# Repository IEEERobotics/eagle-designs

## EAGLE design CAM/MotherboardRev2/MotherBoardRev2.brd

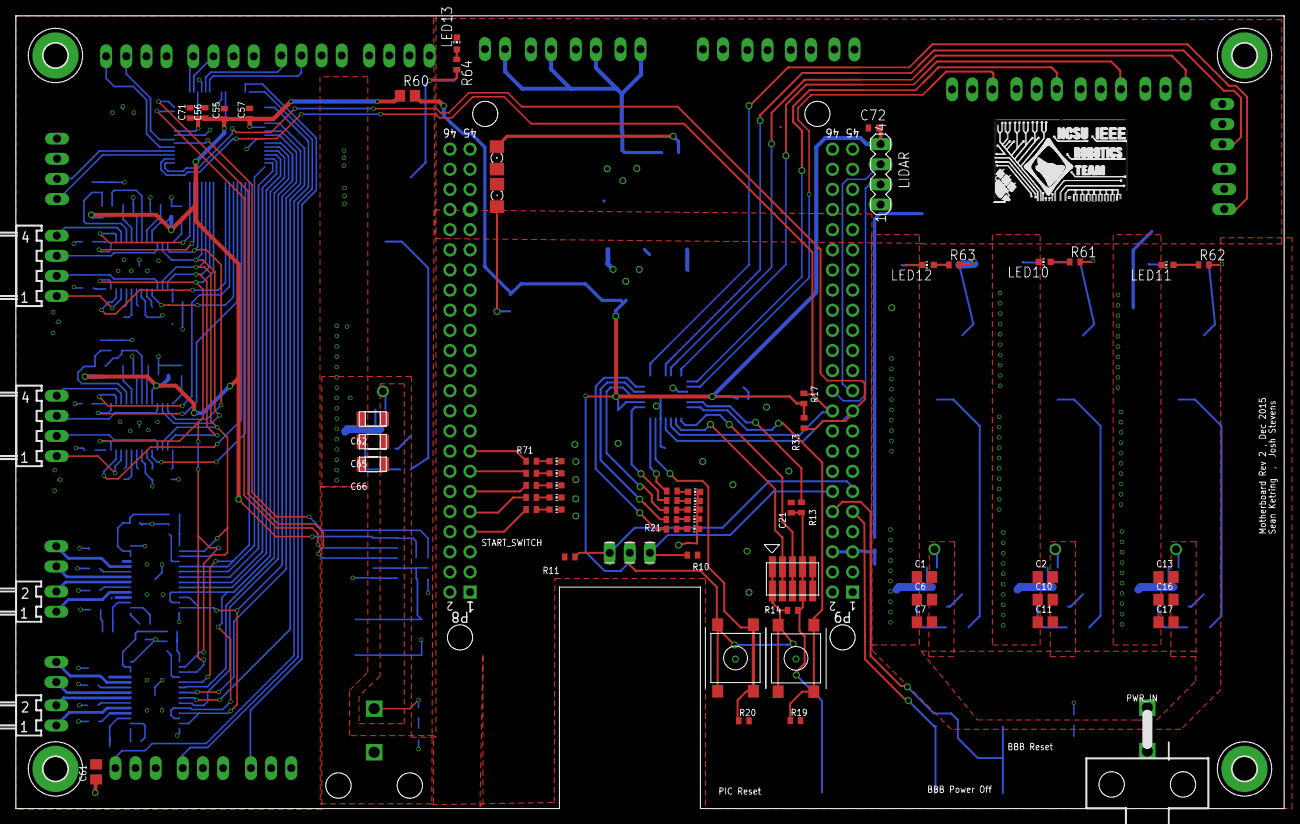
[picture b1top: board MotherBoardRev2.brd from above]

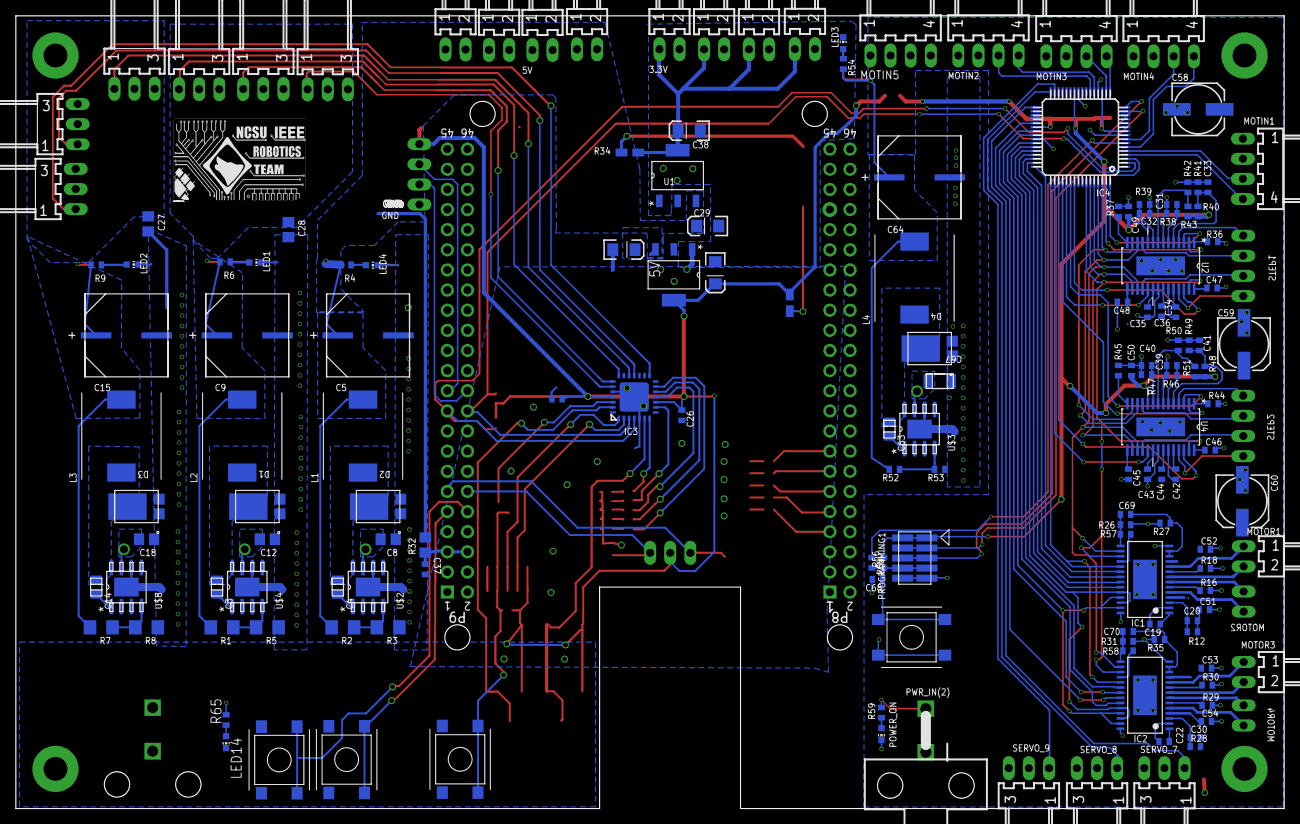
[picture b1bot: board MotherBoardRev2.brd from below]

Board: 2 copper layers, 160.0 x 100.0 mm, 232 parts (157 on the bottom side), 164 nets.

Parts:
3.3V, 3.3V1, 3.3V(2), 3.3V(2)1, 5V, 5V1, 5V(2), 5V(2)1: 7395-02
C1, C2, C6, C7, C8, C10, C11, C12, C13, C16, C17, C18: 4.7uF; C0805
C3, C4, C14, C63: 10nF; 0805
C5, C9, C15, C64: 330uF; SM_RADIAL_10AMM
C19, C22, C51, C52, C53, C54: 0.01uF; C0402
C20, C30, C33, C45, C46, C47, C48, C49, C50, C56, C57, C71: 0.1uF; C0402
C21, C25, C26, C37, C41, C68: .1uF; C0402
C23, C24, C29, C38: 10uF; EIA3216
C27, C28, C61: 10uF; C0805
C31, C32, C39, C40: 1nF; C0402
C34, C35, C36, C42, C43, C44: 0.22uF; C0402
C55: 1uF; C0402
C58, C59, C60: 153CLV-0605
C62, C65, C66, C67: 4.7uF; 1206
C69, C70: 0.47uF; C0402
C72: 4.7uF; C0402
D1, D2, D3, D4: PDS760-13; POWERDI5
D5, D7: 3_3V_PWR; FKIT-LED-1206
H1, H2, H3, H4: MOUNT-PAD-ROUND3.0; 3,0-PAD
IC1, IC2: DRV8814; TSSOP-28
IC3: PIC24FJ64GB202; QFN28-ML_6X6MM
IC4: PIC24FJ256GB106; TQFP64-10X10
L1, L2, L3, L4: WE-HCC_1090
LED1, LED2, LED3, LED4, LED5, LED6, LED7, LED8, LED9, LED10, LED11, LED12, LED13, LED14, LED16, LED17, LED18, LED19, LED20: CHIP-LED0603
LIDAR: MA04-1
MOTIN1, MOTIN2, MOTIN3, MOTIN4, MOTIN5: 22-05-7048-04; 7395-04
MOTOR1, MOTOR2, MOTOR3, MOTOR4: 22-05-7028-02; 7395-02
POWER_ON: CHIP-LED0603
PROGRAMMING, PROGRAMMING1: Jtag; MOTHER-BOARD-REV5_10-PIN-SMD
PWR_IN: 5569-2
PWR_IN(2): 5569-2
R1, R2, R7: 10k; R1206
R3, R5, R8: R1206
R4, R6, R9, R14, R26, R31, R40, R41, R42, R43, R48, R49, R50, R51, R52, R54, R56, R57, R58, R59, R61, R62, R63, R64, R65: 10k; R0402
R10, R11, R19, R20: 10K; R0402
R12, R28: 1M; R0402
R13, R55: 100; R0402
R15, R34: R0805W
R16, R18, R29, R30: 0.2; R0402
R17, R33: 4.7K; R0402
R21, R22, R23, R24, R25: 330; R0402
R27, R35: 30k; R0402
R32: 0 ohm; R0805
R36, R37, R44, R45: 0.1; R0402
R38, R39, R46, R47: 47k; R0402
R53: R0402
R60: R0805
R67, R68, R69, R70, R71: 1K; R0402
SERVO_1, SERVO_2, SERVO_3, SERVO_4, SERVO_5, SERVO_6, SERVO_7, SERVO_8, SERVO_9: 7395-03
START_SWITCH: MA03-1
STEP1, STEP2: 22-05-7048-04; 7395-04
U1, U3: LMS8117AMP-3.3; SOT230P696X180-4N
U2, U4: DRV8811PWP; SOP65P640X120-29N
U$1: BEAGLE_BONE_BLACK_CAPE
U$2, U$3, U$4, U$8: TPS5450DDAR; R-PDSO-G8
U$5, U$9: Switch3; MC32882_FINAL
U$6, U$13, U$14: Switch1; MC32882_FINAL
U$7: Switch2; MC32882_FINAL
U$10, U$11, U$12: LOGO

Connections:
3.3V: C24.A, C25.1, C26.1, C49.1, C50.1, C55.1, C56.1, C57.1, C71.1, C72.1, IC3.10, IC3.25, IC4.10, IC4.19, IC4.26, IC4.38, LIDAR.4, PROGRAMMING.1, PROGRAMMING.2, PROGRAMMING1.1, PROGRAMMING1.2, R14.2, R15.1, R17.2, R33.2, R40.1, R43.1, R48.1, R51.1, R56.2, R60.1, R60.2, START_SWITCH.2, U2.10, U3.4, U4.10, U$6.P$1, U$6.P$4, U$7.P$1, U$7.P$4
+7V: C20.2, C30.2, C36.1, C44.1, C45.1, C46.1, C47.1, C48.1, C51.1, C52.1, C53.1, C54.1, C58.+, C59.+, C60.+, C61.1, C64.1, H4.B3,0, IC1.4, IC1.11, IC2.4, IC2.11, L4.2, MOTIN1.2, MOTIN2.2, MOTIN3.2, MOTIN4.2, MOTIN5.2, MOTIN5.3, R12.2, R28.2, R52.2, R54.2, R64.2, SERVO_7.2, SERVO_8.2, SERVO_9.2, U2.15, U2.28, U4.15, U4.28
BB_PWR_BUTTON: U$1.P9.9, U$13.P$2, U$13.P$3
BB_SYS_RESET: U$1.P9.10, U$14.P$2, U$14.P$3
BOOT1: C4.1, U$2.1
BOOT2: C3.1, U$4.1
BOOT3: C14.1, U$8.1
BOOT_VM: C63.1, U$3.1
CHANNEL_A_1: IC4.4, MOTIN1.4
CHANNEL_A_2: IC4.22, MOTIN2.3
CHANNEL_A_3: IC4.18, MOTIN3.3
CHANNEL_A_4: IC4.8, MOTIN4.3
CHANNEL_B_1: IC4.5, MOTIN1.3
CHANNEL_B_2: IC4.21, MOTIN2.4
CHANNEL_B_3: IC4.17, MOTIN3.4
CHANNEL_B_4: IC4.6, MOTIN4.4
GND: 3.3V.2, 3.3V1.2, 3.3V(2).2, 3.3V(2)1.2, 5V.2, 5V1.2, 5V(2).2, 5V(2)1.2, C1.1, C2.1, C5.2, C6.1, C7.1, C8.1, C9.2, C10.1, C11.1, C12.1, C13.1, C15.2, C16.1, C17.1, C18.1, C21.2, C23.C, C24.C, C25.2, C26.2, C27.2, C28.2, C29.C, C31.2, C32.2, C33.2, C35.2, C37.2, C38.C, C39.2, C40.2, C41.2, C43.2, C45.2, C46.2, C47.2, C48.2, C49.2, C50.2, C51.2, C52.2, C53.2, C54.2, C55.2, C56.2, C57.2, C58.-, C59.-, C60.-, C61.2, C62.1, C64.2, C65.1, C66.1, C67.1, C68.2, C69.2, C70.2, C71.2, C72.2, D1.1, D2.1, D3.1, D4.1, D5.C, D7.C, IC1.14, IC1.28, IC1.EXP, IC2.14, IC2.28, IC2.EXP, IC3.5, IC3.24, IC3.EXP, IC4.9, IC4.20, IC4.25, IC4.41, LED1.C, LED2.C, LED3.C, LED4.C, LED5.C, LED6.C, LED7.C, LED8.C, LED9.C, LED10.C, LED11.C, LED12.C, LED13.C, LED14.C, LED16.C, LED17.C, LED18.C, LED19.C, LED20.C, LIDAR.1, MOTIN1.1, MOTIN2.1, MOTIN3.1, MOTIN4.1, MOTIN5.1, MOTIN5.4, POWER_ON.C, PROGRAMMING.9, PROGRAMMING.10, PROGRAMMING1.9, PROGRAMMING1.10, PWR_IN.1, PWR_IN(2).1, R3.1, R5.1, R8.1, R10.1, R11.1, R16.2, R18.2, R19.2, R20.2, R27.2, R29.2, R30.2, R35.2, R36.2, R37.2, R38.2, R39.2, R41.2, R42.2, R44.2, R45.2, R46.2, R47.2, R49.2, R50.2, R53.1, SERVO_1.3, SERVO_2.3, SERVO_3.3, SERVO_4.3, SERVO_5.3, SERVO_6.3, SERVO_7.3, SERVO_8.3, SERVO_9.3, U1.1, U2.7, U2.21, U2.29, U3.1, U4.7, U4.21, U4.29, U$1.P8.1, U$1.P8.2, U$1.P9.1, U$1.P9.2, U$1.P9.43, U$1.P9.44, U$1.P9.45, U$1.P9.46, U$2.6, U$2.9, U$3.6, U$3.9, U$4.6, U$4.9, U$5.P$1, U$5.P$4, U$8.6, U$8.9, U$9.P$1, U$9.P$4, U$13.P$1, U$13.P$4, U$14.P$1, U$14.P$4
GPIO23: R70.2, U$1.P8.13
GPIO45: R69.2, U$1.P8.11
GPIO47: R71.2, U$1.P8.15
GPIO66: R67.2, U$1.P8.7
GPIO69: R68.2, U$1.P8.9
IO3: IC3.7, R25.2
IO4: IC3.9, R24.2
IO5: IC3.11, R23.2
IO6: IC3.12, R22.2
IO7: IC3.13, R21.2
M1-AENBL: IC1.21, IC4.47
M1-APHASE: IC1.20, IC4.48
M1-BENBL: IC1.22, IC4.46
M1-BHPASE: IC1.23, IC4.45
M1-MAOUT1: IC1.5, MOTOR2.1
M1-MAOUT2: IC1.7, MOTOR2.2
M1-MBOUT1: IC1.10, MOTOR1.1
M1-MBOUT2: IC1.8, MOTOR1.2
M2-AENBL: IC2.21, IC4.39
M2-APHASE: IC2.20, IC4.43
M2-BENBL: IC2.22, IC4.37
M2-BHPASE: IC2.23, IC4.42
M2-MAOUT1: IC2.5, MOTOR4.1
M2-MAOUT2: IC2.7, MOTOR4.2
M2-MBOUT1: IC2.10, MOTOR3.1
M2-MBOUT2: IC2.8, MOTOR3.2
M-DECAY: IC1.19, IC2.19, IC4.49
M-I0: IC1.24, IC1.26, IC2.24, IC2.26, IC4.44
M-I1: IC1.25, IC1.27, IC2.25, IC2.27, IC4.40
M-NSLEEP: IC1.17, IC2.17, IC4.58, U2.27, U4.27
M-RESET: IC1.16, IC2.16, IC4.60, U2.17, U4.17
MCLR: C21.1, PROGRAMMING.7, PROGRAMMING.8, R13.2, R14.1, U$5.P$2, U$5.P$3
MCLR': IC3.26, R13.1
M_MCLR: C68.1, PROGRAMMING1.7, PROGRAMMING1.8, R55.2, R56.1, U$9.P$2, U$9.P$3
M_MCLR': IC4.7, R55.1
M_PGC1: IC4.15, PROGRAMMING1.3, PROGRAMMING1.4
M_PGD1: IC4.16, PROGRAMMING1.5, PROGRAMMING1.6
unnamed: LED4.A, R4.1
unnamed: LED1.A, R6.1
unnamed: LED2.A, R9.1
unnamed: C19.2, IC1.2
unnamed: LED5.A, R21.1
unnamed: LED6.A, R22.1
unnamed: LED7.A, R23.1
unnamed: LED8.A, R24.1
unnamed: LED9.A, R25.1
unnamed: D5.A, R15.2
unnamed: D7.A, R34.2
unnamed: C19.1, IC1.1
unnamed: C20.1, IC1.3, R12.1
unnamed: IC1.6, R16.1
unnamed: IC1.9, R18.1
unnamed: IC1.12, IC1.13, R26.1, R27.1
unnamed: C22.2, IC2.2
unnamed: C37.1, R32.1, U$1.P9.5, U$1.P9.6
unnamed: LED14.A, R65.1
unnamed: C22.1, IC2.1
unnamed: C30.1, IC2.3, R28.1
unnamed: IC2.6, R29.1
unnamed: IC2.9, R30.1
unnamed: IC2.12, IC2.13, R31.1, R35.1
unnamed: IC1.18, R57.1
unnamed: R37.1, U2.14
unnamed: R36.1, U2.1
unnamed: C69.1, IC1.15, R26.2, R57.2
unnamed: C31.1, R38.1, U2.6
unnamed: C32.1, R39.1, U2.9
unnamed: C33.1, R40.2, R41.1, U2.5
unnamed: R42.1, R43.2, U2.8
unnamed: IC2.18, R58.1
unnamed: C34.1, U2.23
unnamed: C70.1, IC2.15, R31.2, R58.2
unnamed: C34.2, U2.24
unnamed: C35.1, U2.20
unnamed: C36.2, U2.22
unnamed: R45.1, U4.14
unnamed: R44.1, U4.1
unnamed: C39.1, R46.1, U4.6
unnamed: C40.1, R47.1, U4.9
unnamed: C41.1, R48.2, R49.1, U4.5
unnamed: R50.1, R51.2, U4.8
unnamed: C42.1, U4.23
unnamed: C42.2, U4.24
unnamed: C43.1, U4.20
unnamed: C44.2, U4.22
unnamed: LED3.A, R54.1
unnamed: POWER_ON.A, R59.1
unnamed: LED16.A, R67.1
unnamed: LED17.A, R68.1
unnamed: LED18.A, R69.1
unnamed: LED19.A, R70.1
unnamed: LED20.A, R71.1
unnamed: LED10.A, R61.1
unnamed: LED11.A, R62.1
unnamed: LED12.A, R63.1
unnamed: LED13.A, R64.1
OC1: IC3.23, SERVO_6.1
OC1': IC4.33, SERVO_7.1
OC2: IC3.22, SERVO_5.1
OC2': IC4.32, SERVO_8.1
OC3: IC3.21, SERVO_4.1
OC3': IC4.31, SERVO_9.1
OC4: IC3.19, SERVO_3.1
OC5: IC3.18, SERVO_2.1
OC6: IC3.15, SERVO_1.1
PGC1: IC3.2, PROGRAMMING.3, PROGRAMMING.4
PGD1: IC3.1, PROGRAMMING.5, PROGRAMMING.6
PH1: C4.2, D2.3, L1.1, U$2.8
PH2: C3.2, D1.3, L2.1, U$4.8
PH3: C14.2, D3.3, L3.1, U$8.8
PH_VM: C63.2, D4.3, L4.1, U$3.8
S1-AOUT1: STEP1.4, U2.4
S1-AOUT2: STEP1.1, U2.25
S1-BOUT1: STEP1.3, U2.11
S1-BOUT2: STEP1.2, U2.18
S1-DIR: IC4.64, U2.3
S1-ENABLEN: IC4.55, U2.26
S1-HOME: IC4.63, U2.2
S1-STEP: IC4.53, U2.19
S2-AOUT1: STEP2.4, U4.4
S2-AOUT2: STEP2.1, U4.25
S2-BOUT1: STEP2.3, U4.11
S2-BOUT2: STEP2.2, U4.18
S2-DIR: IC4.54, U4.3
S2-ENABLEN: IC4.51, U4.26
S2-HOME: IC4.52, U4.2
S2-STEP: IC4.50, U4.19
S-SRN: IC4.59, U2.16, U4.16
SCL: IC3.4, IC4.2, R33.1, U$1.P9.19
SDA: IC3.3, IC4.3, R17.1, U$1.P9.20
START_LEFT: R10.2, START_SWITCH.3, U$1.P9.12
START_RIGHT: R11.2, START_SWITCH.1, U$1.P9.11
SWITCH_1: IC3.27, R19.1, U$6.P$2, U$6.P$3
SWITCH_2: IC3.6, R20.1, U$7.P$2, U$7.P$3
UART_RX: LIDAR.2, U$1.P9.22
UART_TX: LIDAR.3, U$1.P9.21
USM0: IC4.62, U2.13, U4.13
USM1: IC4.61, U2.12, U4.12
VCC: C1.2, C2.2, C6.2, C7.2, C8.2, C10.2, C11.2, C12.2, C13.2, C16.2, C17.2, C18.2, C62.2, C65.2, C66.2, C67.2, PWR_IN.2, PWR_IN(2).2, R59.2, R65.2, U$2.7, U$3.7, U$4.7, U$8.7
VOUT1: 5V.1, 5V1.1, 5V(2).1, 5V(2)1.1, C5.1, C23.A, C29.A, L1.2, R2.2, R4.2, R32.2, R63.2, U1.3, U3.3
VOUT2: C9.1, C28.1, L2.2, R1.2, R6.2, R61.2, SERVO_4.2, SERVO_5.2, SERVO_6.2
VOUT3: C15.1, C27.1, L3.2, R7.2, R9.2, R62.2, SERVO_1.2, SERVO_2.2, SERVO_3.2
VOUT5: 3.3V.1, 3.3V1.1, 3.3V(2).1, 3.3V(2)1.1, C38.A, R34.1, U1.4
VSNS1: R2.1, R3.2, U$2.4
VSNS2: R1.1, R5.2, U$4.4
VSNS3: R7.1, R8.2, U$8.4
VSNS_VM: R52.1, R53.2, U$3.4

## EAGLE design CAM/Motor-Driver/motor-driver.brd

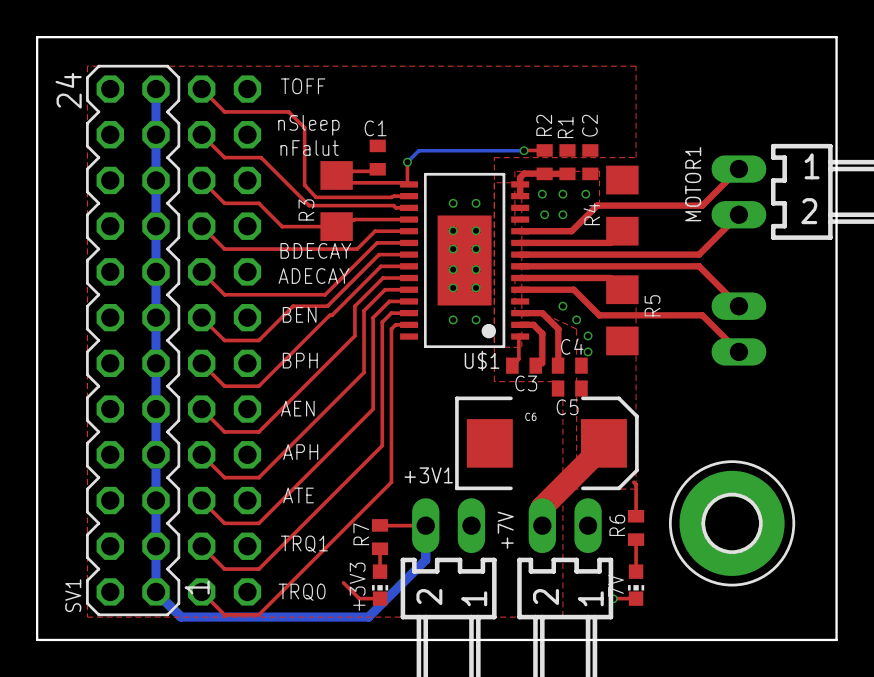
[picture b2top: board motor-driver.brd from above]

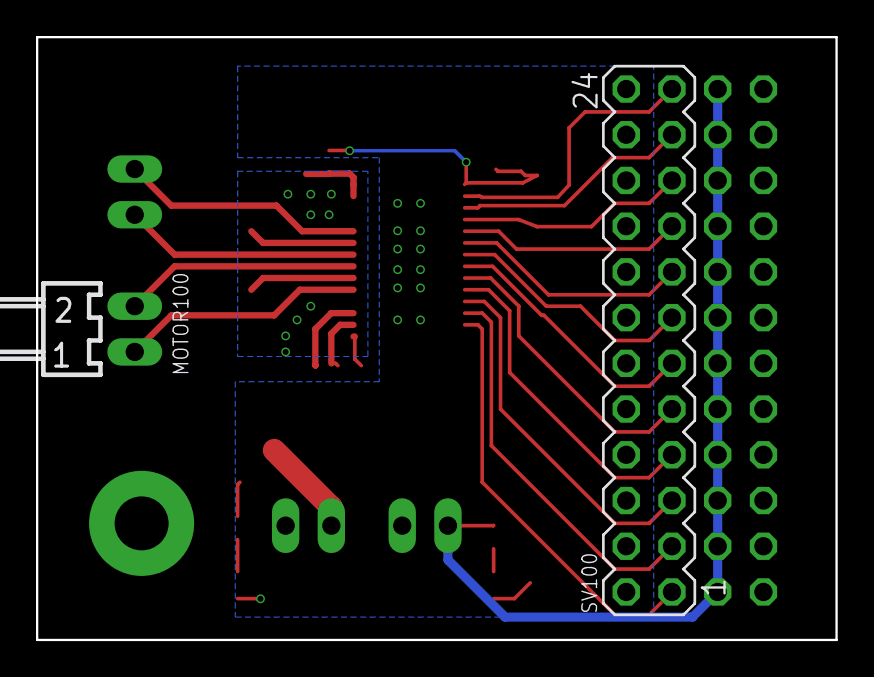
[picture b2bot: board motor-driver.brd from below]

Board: 2 copper layers, 44.4 x 33.5 mm, 23 parts (2 on the bottom side), 28 nets.

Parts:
7V: CHIP-LED0603
+3V1, +7V: 22-05-7028-02; 7395-02
+3V3: CHIP-LED0603
C1, C2, C3, C5: 0.1uF; C0402
C4: 0.47uF; C0402
C6: 100uF; EIA7343
H1: MOUNT-PAD-ROUND3.0; 3,0-PAD
MOTOR1, MOTOR100: 22-05-7028-02; 7395-02
R1, R2: 0.2; R0402
R3: 10K; R1206
R4, R5: R1206
R6: 700; R0402
R7: 330; R0402
SV1, SV100: MA12-2
U$1: DRV8881PPWPR; TSSOP-28

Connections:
+3V3: +3V1.2, R7.2, SV1.1, SV1.3, SV1.5, SV1.7, SV1.9, SV1.11, SV1.13, SV1.15, SV1.17, SV1.19, SV1.21, SV1.23
+7V: +7V.2, C2.1, C4.2, C5.1, C6.A, R6.2, U$1.4, U$1.11
ADECAY: SV100.15, U$1.20
AEN: SV100.9, U$1.23
APH: SV100.7, U$1.24
ATE: SV100.5, U$1.25
BDECAY: SV100.17, U$1.19
BEN: SV100.13, U$1.21
BPH: SV100.11, U$1.22
GND: 7V.C, +3V1.1, +3V3.C, +7V.1, C1.2, C2.2, C5.2, C6.C, R2.2, SV100.2, SV100.4, SV100.6, SV100.8, SV100.10, SV100.12, SV100.14, SV100.16, SV100.18, SV100.20, SV100.22, SV100.24, U$1.12, U$1.28, U$1.EXP
unnamed: R4.1, U$1.9
unnamed: R5.1, U$1.6
unnamed: MOTOR100.1, U$1.5
unnamed: MOTOR100.2, U$1.7
unnamed: MOTOR1.2, U$1.8
unnamed: MOTOR1.1, U$1.10
unnamed: C3.2, U$1.2
unnamed: C3.1, U$1.1
unnamed: C4.1, U$1.3
unnamed: +3V3.A, R7.1
unnamed: 7V.A, R6.1
unnamed: R1.2, R2.1, U$1.13, U$1.14
NFAULT: R3.1, SV100.19, U$1.18
NSLEEP: SV100.21, U$1.17
TOFF: SV100.23, U$1.16
TRQ0: SV100.1, U$1.27
TRQ1: SV100.3, U$1.26
V3P3: C1.1, R1.1, R3.2, U$1.15

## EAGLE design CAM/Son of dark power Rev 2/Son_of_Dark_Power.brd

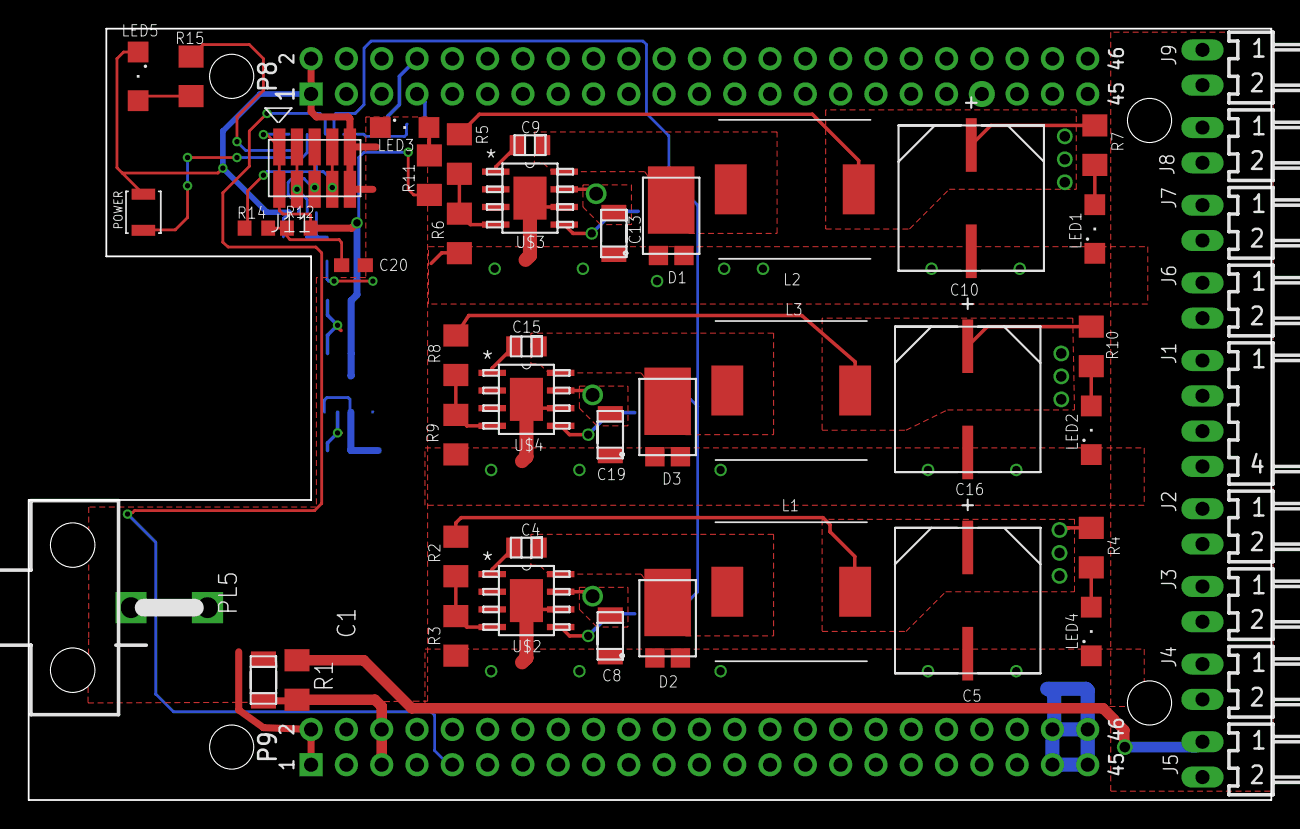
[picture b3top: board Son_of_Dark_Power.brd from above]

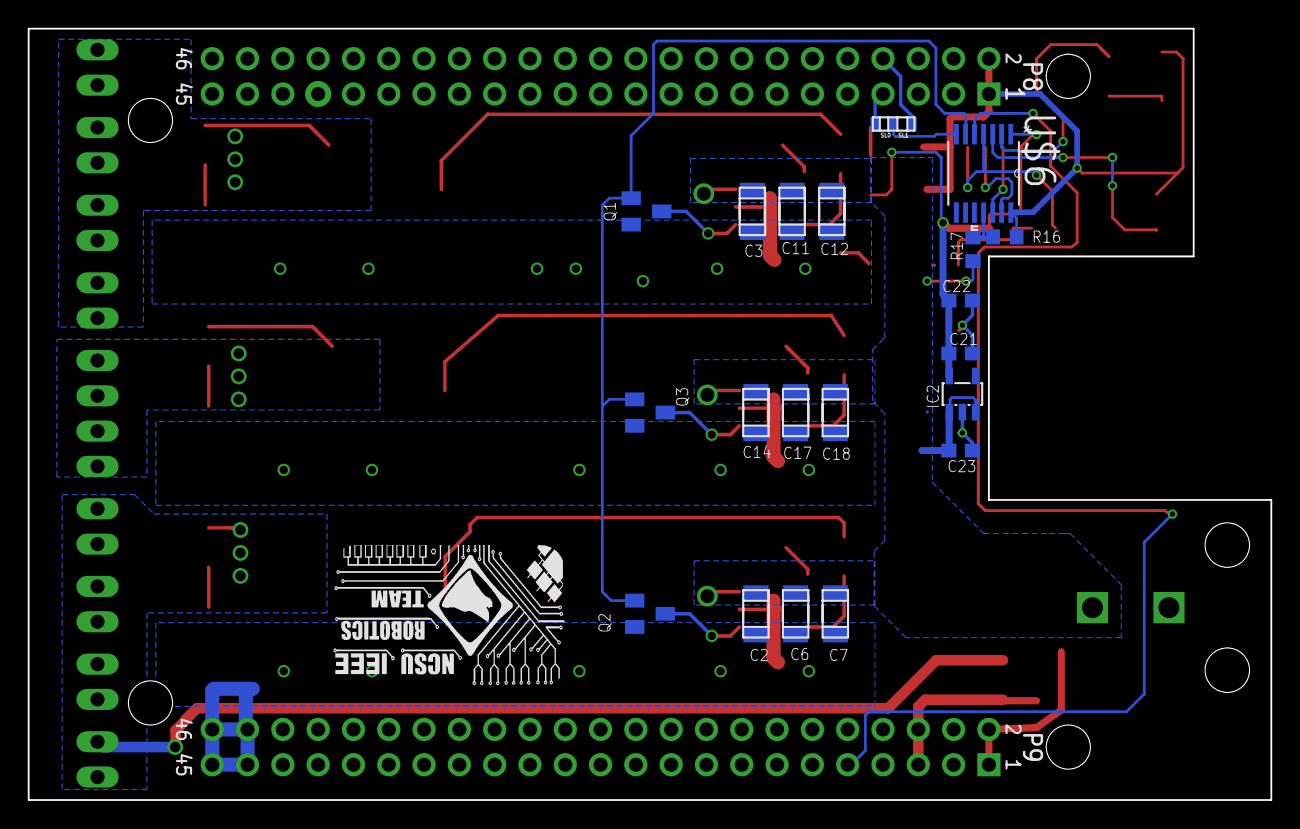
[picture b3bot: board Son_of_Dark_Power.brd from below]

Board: 2 copper layers, 89.4 x 55.5 mm, 73 parts (21 on the bottom side), 36 nets.

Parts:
C1: .1uF; 1206
C2, C3, C6, C7, C8, C11, C12, C13, C14, C17, C18, C19: 4.7uF; 1206
C4, C9, C15: 10nF; 0805
C5, C10, C16: 330uF; SM_RADIAL_10AMM
C20: 2.2nF; C0603
C21, C22, C23: C0603
D1, D2, D3: PDS760-13; POWERDI5
IC2: TS5205; SOT25
J1: 22-05-7048-04; 7395-04
J2, J3, J4, J5, J6, J7, J8, J9: 22-05-7028-02; 7395-02
J11: PIN-CONNECTOR74089; 10-PIN-SMD
L1, L2, L3: WE-HCC_1090
LED1, LED2, LED3, LED4, LED5: SML1206
PL5: 5569-2
POWER: SPST-2_5X4; SPST-TAC-4X2_5MM
Q1, Q2, Q3: BSS123; SOT23
R1: 0 ohm; R1206
R2, R4, R5, R7, R8, R10, R11, R15: 10k; R1206
R3, R6, R9: R1206
R12: 49.9k; R0603
R14: 220; R0603
R16: 1.24k; R0603
R17: 10k; R0603
SPDT: SPDT_SWITCH; SPDT
U$1: BEAGLE_BONE_BLACK_CAPE
U$2, U$3, U$4: TPS5450DDAR; R-PDSO-G8
U$5: LOGO-IEEE; LOGO
U$6: PIC16F676-I/ST; SOP65P640X120-14N

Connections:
+3V3: C21.1, C22.1, IC2.5, J11.1, J11.2, R11.2, R12.2, U$6.1
+5V: C5.1, J2.1, J3.1, J4.1, J5.1, L1.2, R1.2, R2.2, R4.2
BB_PWR_SW: U$1.P9.9, U$6.5
BOOT_5: C4.1, U$2.1
BOOT_6: C9.1, U$3.1
BOOT_MOTOR: C15.1, U$4.1
EN: Q1.1, Q2.1, Q3.1, U$6.6
ENA_5: Q2.3, U$2.5
ENA_6: Q1.3, U$3.5
ENA_MOTOR: Q3.3, U$4.5
GND: C1.2, C2.1, C3.1, C5.2, C6.1, C7.1, C8.1, C10.2, C11.1, C12.1, C13.1, C14.1, C16.2, C17.1, C18.1, C19.1, C20.2, C21.2, C22.2, C23.2, D1.1, D2.1, D3.1, IC2.2, J1.1, J1.4, J2.2, J3.2, J4.2, J5.2, J6.2, J7.2, J8.2, J9.2, J11.9, J11.10, LED1.C, LED2.C, LED3.C, LED4.C, LED5.C, PL5.1, POWER.P$2, Q1.2, Q2.2, Q3.2, R3.1, R6.1, R9.1, R16.2, U$1.P8.1, U$1.P8.2, U$1.P9.1, U$1.P9.2, U$1.P9.43, U$1.P9.44, U$1.P9.45, U$1.P9.46, U$2.6, U$2.9, U$3.6, U$3.9, U$4.6, U$4.9, U$6.14
ICSPCLK: J11.3, J11.4, U$6.12
ICSPDAT: J11.5, J11.6, U$6.13
unnamed: C1.1, R1.1, U$1.P9.5, U$1.P9.6
unnamed: LED4.A, R4.1
unnamed: LED1.A, R7.1
unnamed: LED2.A, R10.1
unnamed: C20.1, R12.1, R14.1
unnamed: LED3.A, R11.1
unnamed: R16.1, R17.2, U$6.11
unnamed: R15.2, U$6.2
unnamed: LED5.A, R15.1
unnamed: POWER.P$1, U$6.3
unnamed: SPDT.1, U$1.P8.7
unnamed: SPDT.3, U$1.P8.8
PH_5: C4.2, D2.3, L1.1, U$2.8
PH_6: C9.2, D1.3, L2.1, U$3.8
PH_MOTOR: C15.2, D3.3, L3.1, U$4.8
POWER_SIG: SPDT.2, U$6.7
VCC: C2.2, C3.2, C6.2, C7.2, C8.2, C11.2, C12.2, C13.2, C14.2, C17.2, C18.2, C19.2, C23.1, IC2.1, IC2.3, PL5.2, R17.1, U$2.7, U$3.7, U$4.7
VOUT_6: C10.1, J6.1, J7.1, J8.1, J9.1, L2.2, R5.2, R7.2
VOUT_MOTOR: C16.1, J1.2, J1.3, L3.2, R8.2, R10.2
VPP/MCLR: J11.7, J11.8, R14.2, U$6.4
VSNS1_MOTOR: R8.1, R9.2, U$4.4
VSNS_5: R2.1, R3.2, U$2.4
VSNS_6: R5.1, R6.2, U$3.4

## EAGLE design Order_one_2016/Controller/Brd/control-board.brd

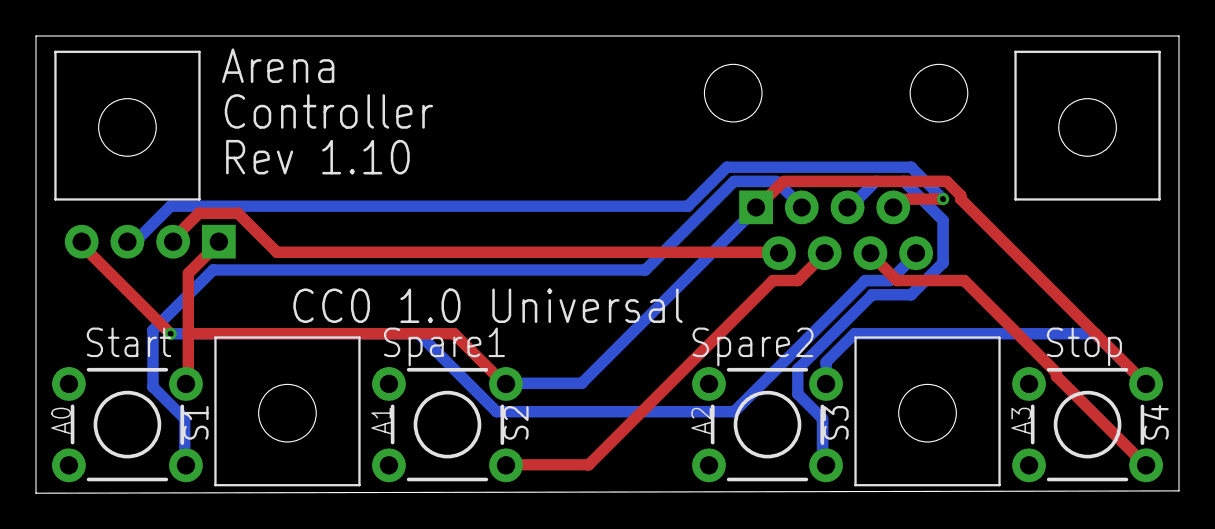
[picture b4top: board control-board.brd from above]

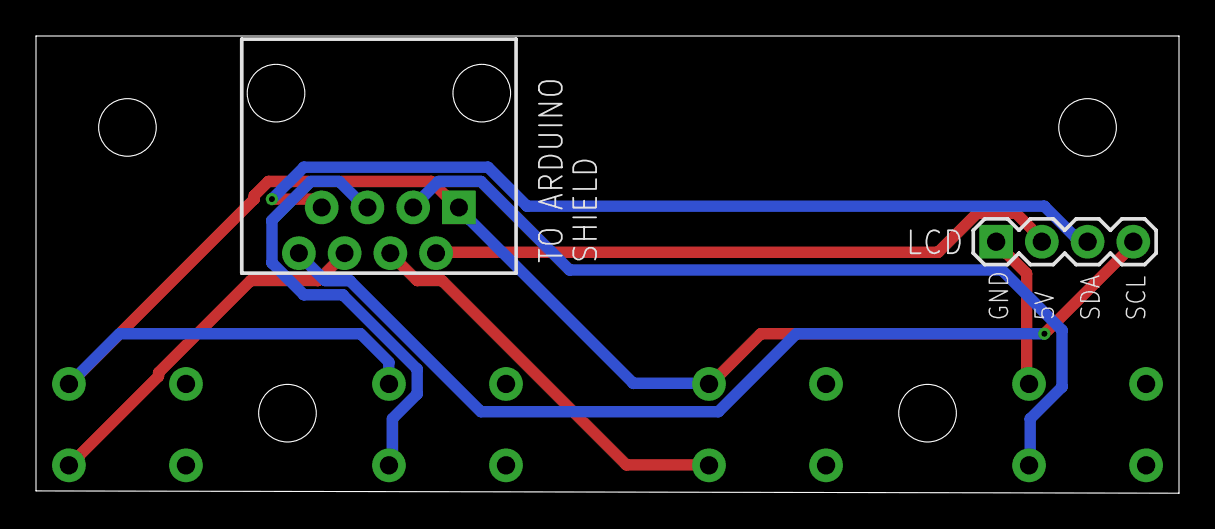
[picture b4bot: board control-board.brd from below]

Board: 2 copper layers, 63.5 x 25.4 mm, 10 parts (2 on the bottom side), 8 nets.

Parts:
JP1: LCD; 1X04
JP2: SHIELD; RJ45-8
MT1, MT2, MT3, MT4: 3.2-MOUNT
S1, S2, S3, S4: SWITCH-MOMENTARY-2PTH; TACTILE-PTH

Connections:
5V: JP1.2, JP2.2
A0: JP2.3, S1.1
A1: JP2.4, S2.1
A2: JP2.5, S3.1
A3: JP2.6, S4.1
A4-SDA: JP1.3, JP2.7
A5-SCL: JP1.4, JP2.8
GND: JP1.1, JP2.1, S1.3, S2.3, S3.3, S4.3

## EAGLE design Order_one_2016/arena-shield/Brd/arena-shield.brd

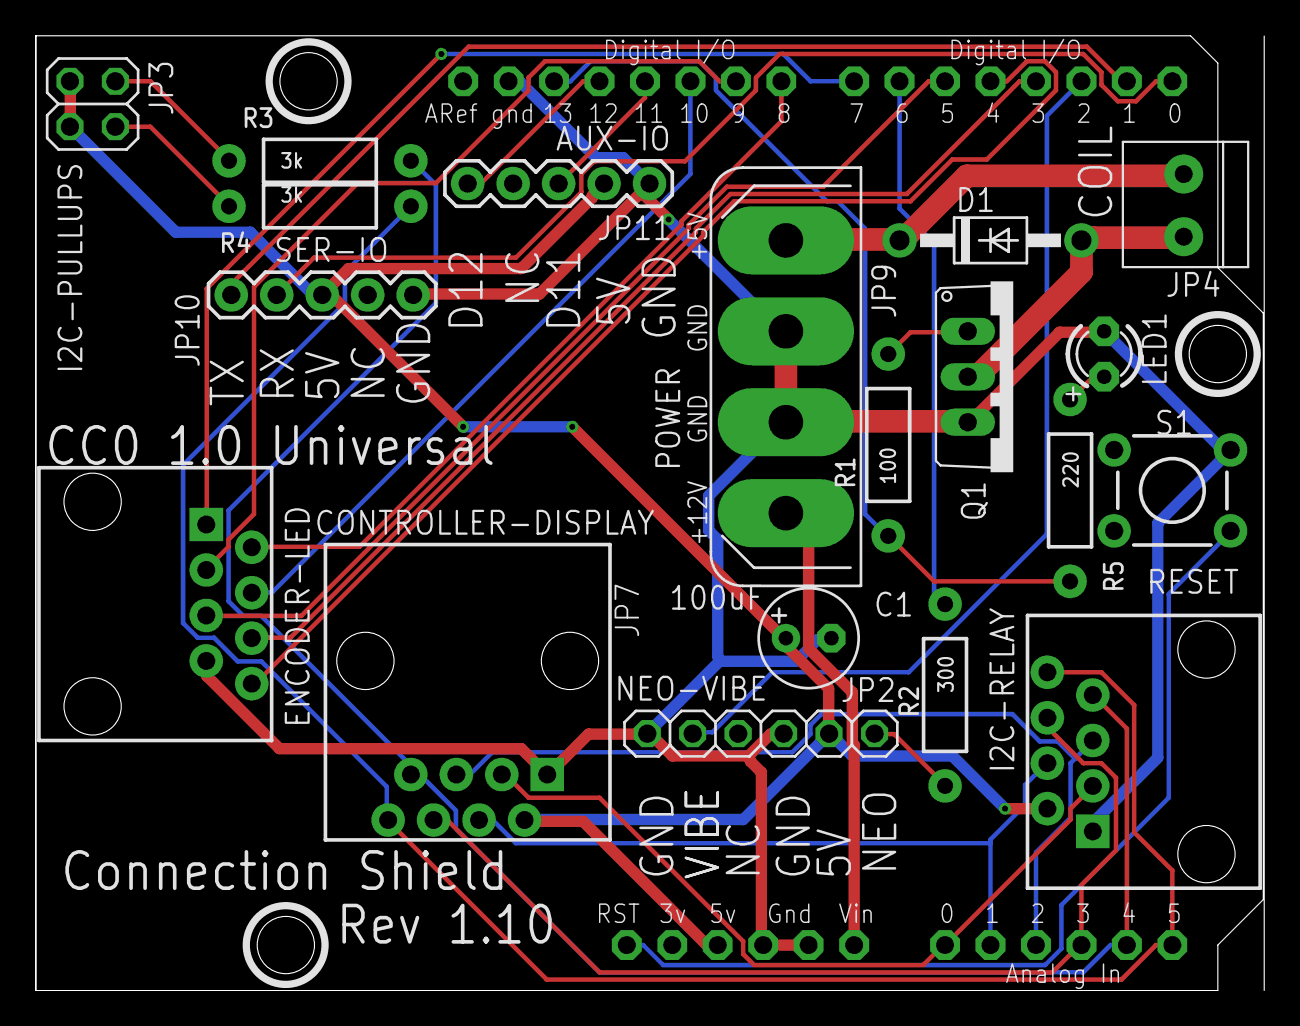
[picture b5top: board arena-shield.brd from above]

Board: 2 copper layers, 68.6 x 53.3 mm, 20 parts (0 on the bottom side), 31 nets.

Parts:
C1: 100uF; E2,5-6
D1: 1N4004; DO41-10
JP2: NEO-VIBE; 1X06
JP3: I2C-PULLUPS; 2X02
JP4: COIL; 1X2-3.5MM
JP6: ENCODER-LED; RJ45-8
JP7: CONTROLLER-DISPLAY; RJ45-UPRIGHT
JP8: I2C-RELAY; RJ45-8
JP9: POWER; FLOPPY-4
JP10: SER-IO; 1X05
JP11: AUX-IO; 1X05
LED1: MAGNET; LED3MM
Q1: IRLB8721PbF; TO220V
R1: 100; AXIAL-0.4
R2: 300; AXIAL-0.4
R3, R4: 3k; AXIAL-0.4
R5: 220; AXIAL-0.4
S1: RESET; TACTILE-PTH
U$1: ARDUINOUNO; ARDUINO

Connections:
12V_PS_POS: JP9.4, U$1.VIN
+5V: C1.+, JP2.5, JP3.1, JP3.3, JP7.2, JP8.2, JP10.3, JP11.2, U$1.5V
A0: JP7.3, JP8.3, U$1.A0
A1: JP7.4, JP8.4, U$1.A1
A2: JP7.5, JP8.5, U$1.A2
A3: JP7.6, JP8.6, U$1.A3
BLUE: JP6.4, U$1.D10
COIL_5V: D1.C, JP4.1, JP9.1
COIL_RETURN: D1.A, JP4.2, Q1.2
D11: JP11.3, U$1.D11
D12: JP11.5, U$1.D12
GND: C1.-, JP2.1, JP2.4, JP6.7, JP7.1, JP8.1, JP9.2, JP9.3, JP10.1, JP11.1, LED1.K, Q1.3, S1.3, U$1.GND, U$1.GND1, U$1.GND2
GREEN: JP6.3, U$1.D9
LED-SWITCH-COM: JP6.1, U$1.D7
unnamed: R1.P$1, R5.P$2, U$1.D13
unnamed: LED1.A, R5.P$1
unnamed: S1.1, U$1.RESET
unnamed: JP3.4, R4.P$1
unnamed: JP3.2, R3.P$1
unnamed: Q1.1, R1.P$2
unnamed: R2.P$1, U$1.D6
NEO-DATA: JP2.6, R2.P$2
PUSHBUTTON: JP6.5, U$1.D5
QUAD-A: JP6.8, U$1.D4
QUAD-B: JP6.6, U$1.D3
RED: JP6.2, U$1.D8
RX: JP10.4, U$1.D0
SCL: JP7.8, JP8.8, R4.P$2, U$1.A5
SDA: JP7.7, JP8.7, R3.P$2, U$1.A4
TX: JP10.5, U$1.D1
VIBRATE: JP2.2, U$1.D2

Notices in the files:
Order_one_2016/Controller/Brd/control-board.brd:
CC0 1.0 Universal
parts and their libraries:
SparkFun-Capacitors: Licensing: Creative Commons ShareAlike 4.0 International - https://creativecommons.org/licenses/by-sa/4.0
SparkFun-Connectors: Licensing: CC v3.0 Share-Alike You are welcome to use this library for commercial purposes.
